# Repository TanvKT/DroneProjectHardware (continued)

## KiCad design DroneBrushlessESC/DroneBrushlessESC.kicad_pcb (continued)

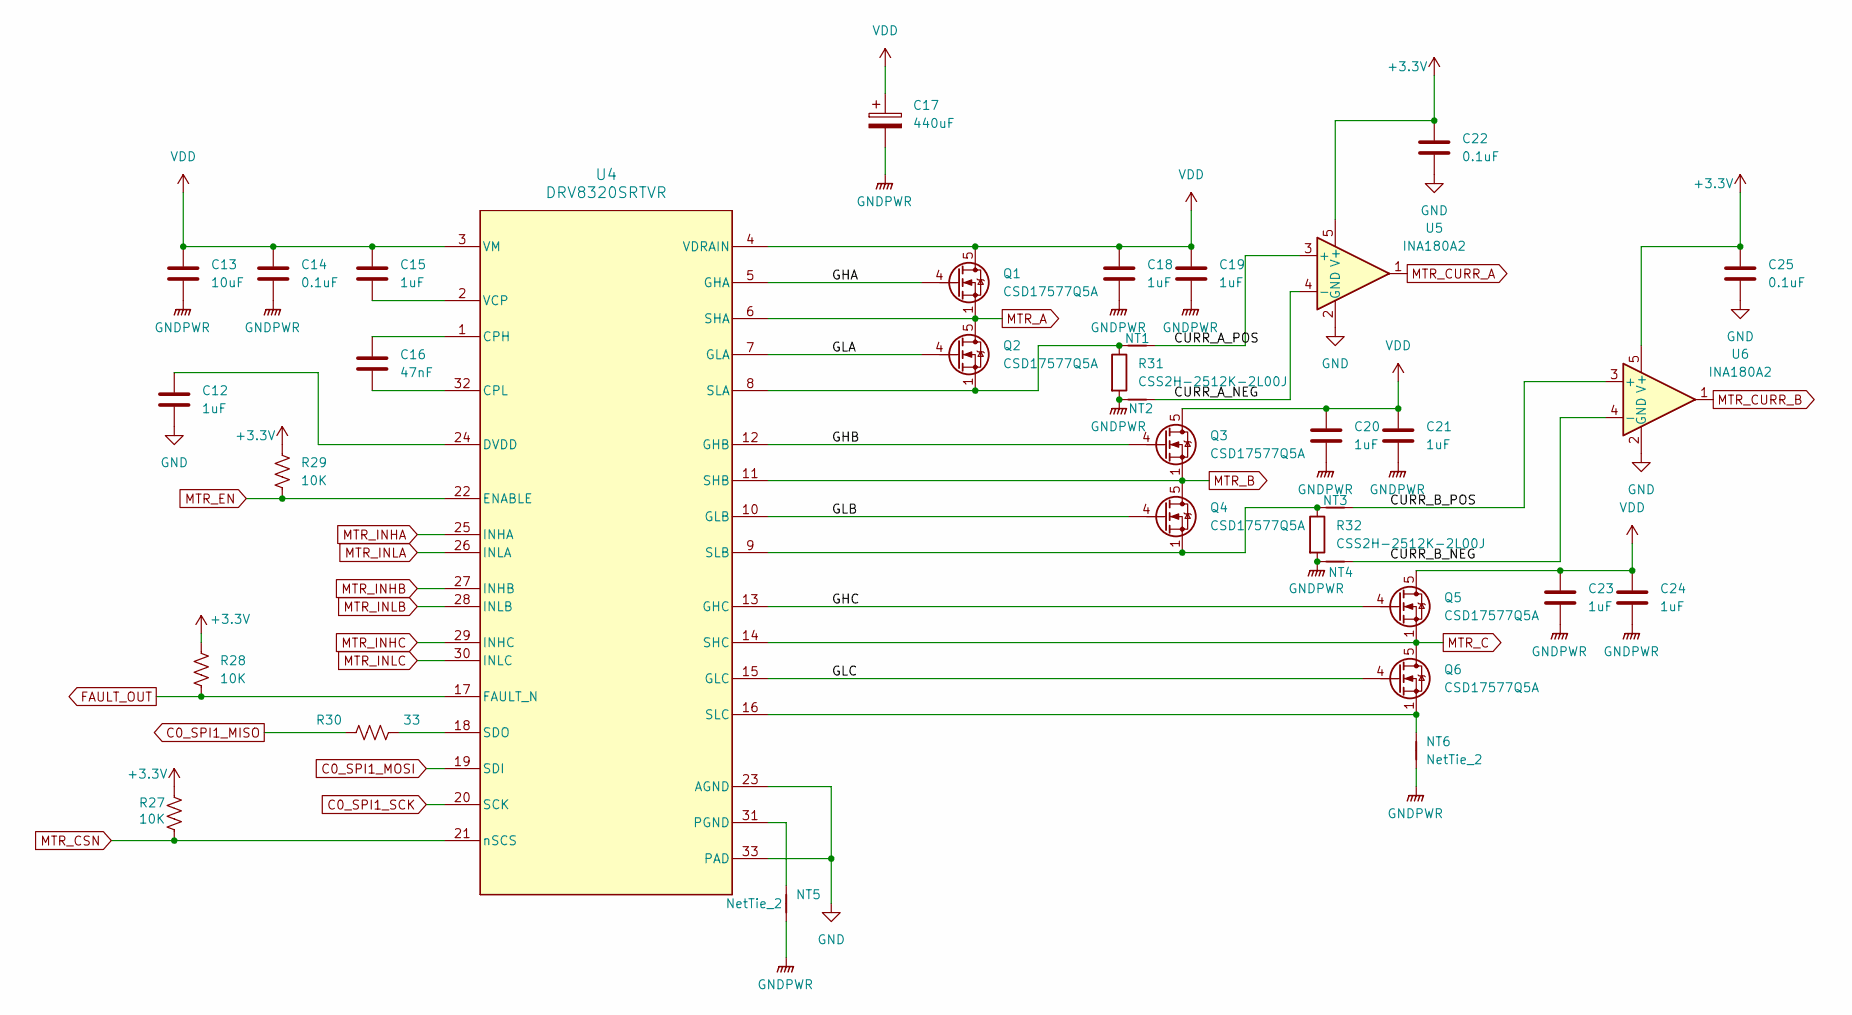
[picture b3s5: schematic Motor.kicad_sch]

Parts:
C12, C15: 1uF; C_0402_1005Metric
C13: 10uF; C_1206_3216Metric
C14, C22, C25: 0.1uF; C_0402_1005Metric
C16: 47nF; C_0402_1005Metric
C17: 440uF; CP_Radial_D10.0mm_P5.00mm
C18, C19, C20, C21, C23, C24: 1uF; C_0603_1608Metric
NT1, NT2, NT3, NT4, NT5, NT6: NetTie_2; NetTie-2_SMD_Pad0.5mm
Q1, Q2, Q3, Q4, Q5, Q6: CSD17577Q5A; TDSON-8-1
R27, R28, R29: 10K; R_0402_1005Metric
R30: 33; R_0402_1005Metric
R31, R32: CSS2H-2512K-2L00J; R_2512_6332Metric
U4: DRV8320SRTVR
U5, U6: INA180A2; SOT-23-5

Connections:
+3.3V: C22.1, C25.1, R27.2, R28.2, R29.2, U5.5 (V+), U6.5 (V+); also elsewhere on the board
/Motor/CURR_A_NEG: NT2.2, U5.4 (-)
/Motor/CURR_A_POS: NT1.2, U5.3 (+)
/Motor/CURR_B_NEG: NT4.2, U6.4 (-)
/Motor/CURR_B_POS: NT3.2, U6.3 (+)
/Motor/GHA: Q1.4 (G), U4.5 (GHA)
/Motor/GHB: Q3.4 (G), U4.12 (GHB)
/Motor/GHC: Q5.4 (G), U4.13 (GHC)
/Motor/GLA: Q2.4 (G), U4.7 (GLA)
/Motor/GLB: Q4.4 (G), U4.10 (GLB)
/Motor/GLC: Q6.4 (G), U4.15 (GLC)
C0_SPI1_MISO: R30.1; also elsewhere on the board
C0_SPI1_MOSI: U4.19 (SDI); also elsewhere on the board
C0_SPI1_SCK: U4.20 (SCK); also elsewhere on the board
FAULT_OUT: R28.1, U4.17 (FAULT_N); also elsewhere on the board
GND: C12.2, C22.2, C25.2, U4.23 (AGND), U4.33 (PAD), U5.2 (GND), U6.2 (GND); also elsewhere on the board
GNDPWR: C13.2, C14.2, C17.2, C18.2, C19.2, C20.2, C21.2, C23.2, C24.2, NT2.1, NT4.1, NT5.1, NT6.1, R31.2, R32.2; also elsewhere on the board
MTR_A: Q1.1 (S), Q1.2 (S), Q1.3 (S), Q2.5 (D), U4.6 (SHA); also elsewhere on the board
MTR_B: Q3.1 (S), Q3.2 (S), Q3.3 (S), Q4.5 (D), U4.11 (SHB); also elsewhere on the board
MTR_C: Q5.1 (S), Q5.2 (S), Q5.3 (S), Q6.5 (D), U4.14 (SHC); also elsewhere on the board
MTR_CSN: R27.1, U4.21 (nSCS); also elsewhere on the board
MTR_CURR_A: U5.1; also elsewhere on the board
MTR_CURR_B: U6.1; also elsewhere on the board
MTR_EN: R29.1, U4.22 (ENABLE); also elsewhere on the board
MTR_INHA: U4.25 (INHA); also elsewhere on the board
MTR_INHB: U4.27 (INHB); also elsewhere on the board
MTR_INHC: U4.29 (INHC); also elsewhere on the board
MTR_INLA: U4.26 (INLA); also elsewhere on the board
MTR_INLB: U4.28 (INLB); also elsewhere on the board
MTR_INLC: U4.30 (INLC); also elsewhere on the board
unnamed: C16.2, U4.1 (CPH)
unnamed: C16.1, U4.32 (CPL)
unnamed: C12.1, U4.24 (DVDD)
unnamed: NT5.2, U4.31 (PGND)
unnamed: R30.2, U4.18 (SDO)
unnamed: NT1.1, Q2.1 (S), Q2.2 (S), Q2.3 (S), R31.1, U4.8 (SLA)
unnamed: NT3.1, Q4.1 (S), Q4.2 (S), Q4.3 (S), R32.1, U4.9 (SLB)
unnamed: NT6.2, Q6.1 (S), Q6.2 (S), Q6.3 (S), U4.16 (SLC)
unnamed: C15.2, U4.2 (VCP)
VDD: C13.1, C14.1, C15.1, C17.1, C18.1, C19.1, C20.1, C21.1, C23.1, C24.1, Q1.5 (D), Q3.5 (D), Q5.5 (D), U4.3 (VM), U4.4 (VDRAIN); also elsewhere on the board

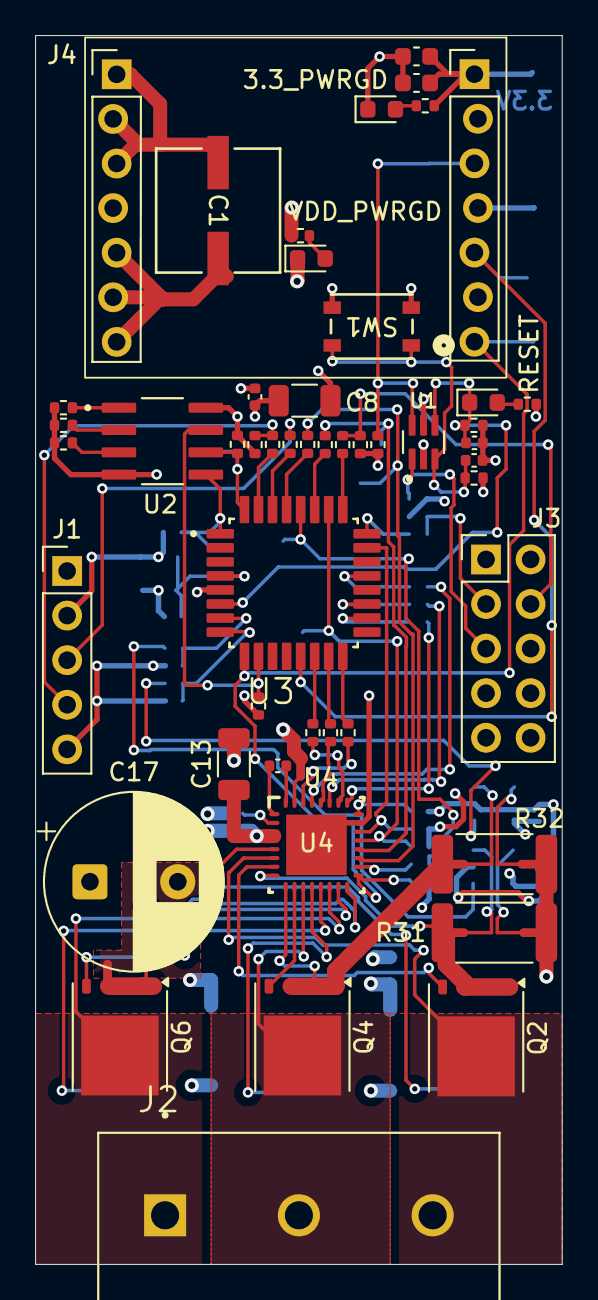
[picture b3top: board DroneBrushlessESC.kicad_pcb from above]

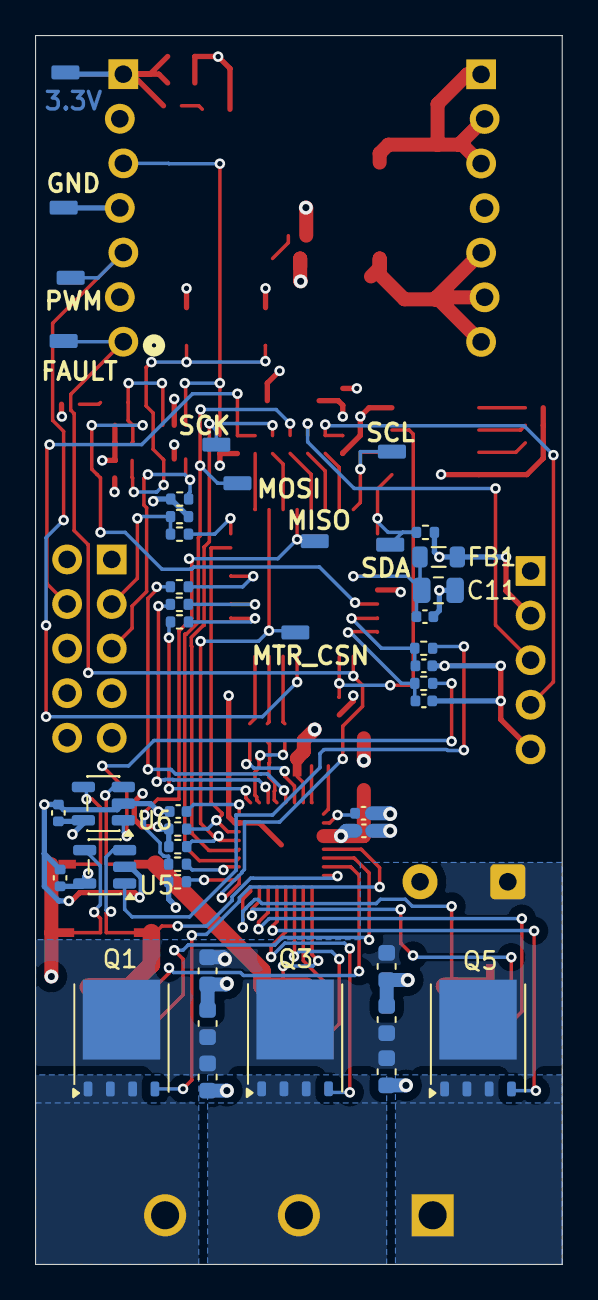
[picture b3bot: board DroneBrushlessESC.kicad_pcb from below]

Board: 4 copper layers, 30.0 x 70.0 mm, 98 parts (44 on the bottom side), 73 nets.

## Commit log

2026-01-28 Base Project
2026-02-01 Initial Prototype Schematic for testing MCU and various sensors complete
2026-02-01 Added test points
2026-02-03 Added mounting holes and some more testpoints. Also started on PCB with dimesions and mounting holes measured and placed
2026-02-05 Finished initial PCB layout. However decided to go ahead and add the motor drivers for the first prototype anyways. Re-did the reverse-polarity detection to use an NMOS instead of a PMOS. Added sheet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
2026-02-05 Re-did layout for new power system
2026-02-08 Added a second MCU for motor control. Removed 5V rail. Added COM switching for SWD and UART external headers
2026-02-08 removed q file
2026-02-09 Changed motor controller to higher pin count MCU. Defined all the pins for 3x PWM control over 4 motors. Renamed a couple of global IO signals to indicate MCU origin (C0 vs C1)
2026-02-11 Finished motor and C1 designs, still need to rename components on MTR2, 3, and 4 pages
2026-02-18 Finished most of routing for motor controls, however likely going to revert back and make separate ESC boards for motor control as I think that would honestly be more efficient from both a cost and d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
2026-02-18 Removed C1 and motor controllers from main platform and moved to own project
2026-02-19 Completed schematic for brushless ESC and added needed components to main board. The plan is to mount the ESCs on the main board using 2.54mm Vert Conn Headers
2026-02-20 Finished layout for controller board
2026-02-22 Finished brushless driver layout
2026-02-24 Finished Schematic for controller
2026-02-24 Finished layout for controller, ready to order REV 0-1 PCBs
2026-02-24 Swapped polarity of joystick and speed dial so that values line up correctly with desired control. In short 3.3V on ADC is max speed rather than no speed.
